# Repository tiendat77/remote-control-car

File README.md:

# Remote Control Car Project
> Remote control car with android and esp32

This project aims to build a Remote Control Car (RC Car) with Espressif ESP32 and Android Remote Control Application.

## Requirements :alien:
1. RC Car. Check out [building instructions](https://github.com/tiendat77/remote-control-car/tree/master/rc-car)
2. Android phone running 5.0 (Lollipop) or higher
3. WiFi network

## Usage :book:
1. Upload [the sketch](https://github.com/tiendat77/remote-control-car/blob/master/rc-car/rc-car.ino) to the RC Car via [Arduino IDE](https://www.arduino.cc/en/software)
2. Install [Car Controller](https://github.com/tiendat77/remote-control-car/blob/master/CarController.apk) application to your smartphone
3. Connect RC Car and your smartphone to the same WiFi network
4. Open Car Controller application, then open *App Settings* and make sure *RC Car IP Address* is correct.
5. Click `Connect Button` on the top left corner of the screen. *Light bulb on is connected*.
6. Enjoy!

## Features :muscle:
- Stable connection.
- Obstacles detection.
- Changeable themes.
- Supports 3 type of control: buttons, joystick, motion sensor (tilt to turn).

## Demos :boom:

## Future plans :eyes:

  - [ ] Install camera
  - [ ] Build wireless handle remote controller

## Contributing :sparkles:

If you have any problem from installation, please [open an issue](https://github.com/tiendat77/remote-control-car/issues/new).

Contributions of any kind are definitely welcome!

## Open source libraries
- [virtual-joystick-android](https://github.com/controlwear/virtual-joystick-android)

## License

MIT © 2020 [TienDat](mailto:huynhztienzdat@gmail.com), see [the license](https://github.com/tiendat77/remote-control-car/blob/master/LICENSE).

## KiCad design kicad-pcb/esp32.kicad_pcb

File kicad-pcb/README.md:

# KiCad
> KiCad is a free software suite for electronic design automation. It facilitates the design of schematics for electronic circuits and their conversion to PCB designs.

## Installation

[Download instructions](https://kicad.org/download/)

Install KiCad on Ubuntu, enter these commands into terminal:

```
sudo add-apt-repository --yes ppa:kicad/kicad-5.1-releases
sudo apt update
sudo apt install --install-recommends kicad

# If you want demo projects
sudo apt install kicad-demos
```

## RC Car Schematic
| PIN         | FUNCTION    | Description        |
| ----------- | ----------- | ------------------ |
| GPIO4       | L298N IN1   | L298N INPUT 1 (A1) |
| GPIO0       | L298N IN2   | L298N INPUT 2 (A2) |
| GPIO2       | L298N IN3   | L298N INPUT 3 (B1) |
| GPIO15      | L298N IN4   | L298N INPUT 4 (B2) |
| GPIO12      | SRF05 TRIG  | SRF05 TRIG (INPUT) |
| GPIO14      | SRF05 ECHO  | SRF05 ECHO (OUTPUT)|
| GPIO25      | SIGNAL      | WiFi connection status |
| GPIO33      | FUNCTION 1  | Headlight |
| GPIO32      | FUNCTION 2  | Left turn signal lights |
| GPIO35      | FUNCTION 3  | Right turn signal lights |
| GPIO34      | FUNCTION 4  | Horn |

## RC Car PCB
<table>
  <tr>
    <td></td>
    <td></td>
  </tr>
</table>

[PDF](https://github.com/tiendat77/remote-control-car/blob/master/assets/rc_car_pcb.pdf)

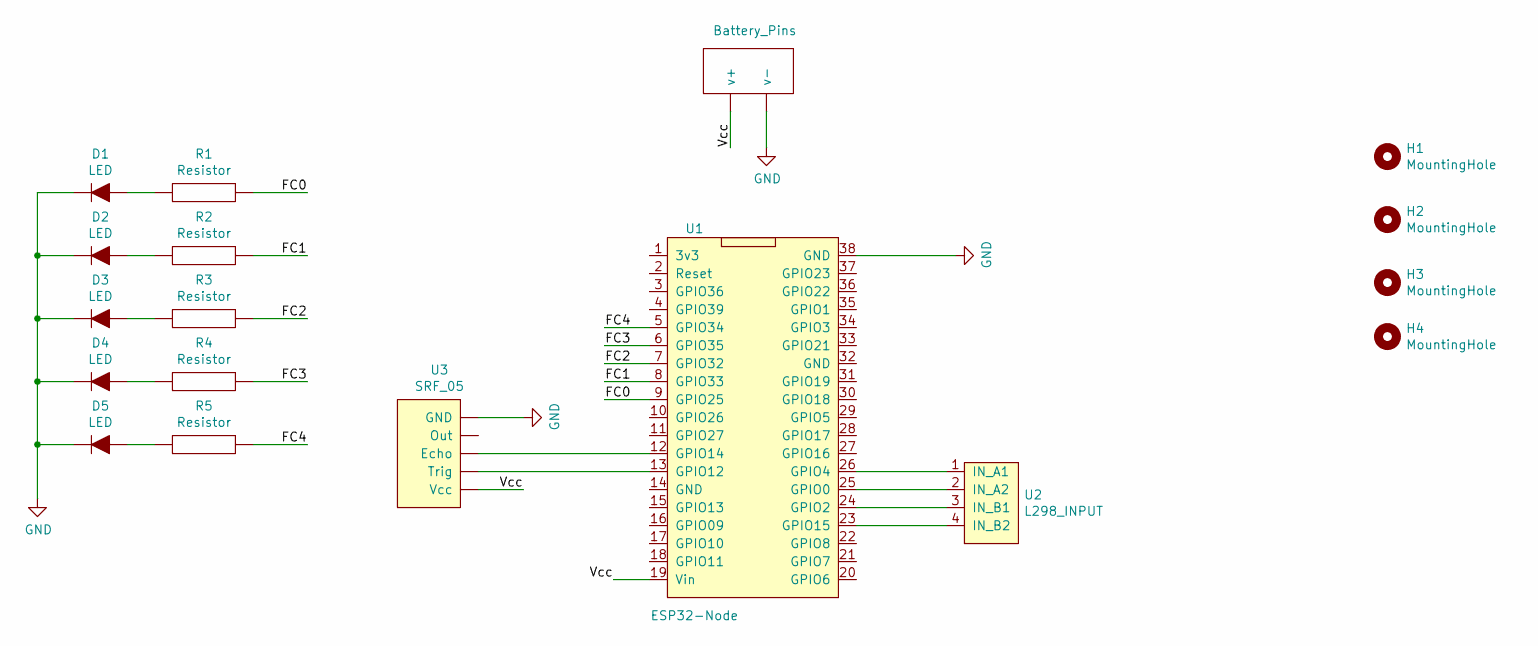
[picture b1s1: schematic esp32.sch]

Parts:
BT1: Battery_Pins; Domino_2_5.05mm
D1, D2, D3, D4, D5: LED; Led
H1, H2, H3, H4: MountingHole
R1, R2, R3, R4, R5: Resistor
U1: ESP32-Node; ESP32_Node
U2: L298_INPUT; L298_Input
U3: SRF_05; SRF05

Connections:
/FC0: R1.2, U1.9 (GPIO25)
/FC1: R2.2, U1.8 (GPIO33)
/FC2: R3.2, U1.7 (GPIO32)
/FC3: R4.2, U1.6 (GPIO35)
/FC4: R5.2, U1.5 (GPIO34)
/Vcc: BT1.1 (v+), U1.19 (Vin), U3.1 (Vcc)
GND: BT1.2 (v-), D1.2, D2.2, D3.2, D4.2, D5.2, U1.38 (GND), U3.5 (GND)
unnamed: D1.1, R1.1
unnamed: D2.1, R2.1
unnamed: D3.1, R3.1
unnamed: D4.1, R4.1
unnamed: D5.1, R5.1
unnamed: U1.12 (GPIO14), U3.3 (Echo)
unnamed: U1.13 (GPIO12), U3.2 (Trig)
unnamed: U1.23 (GPIO15), U2.4 (IN_B2)
unnamed: U1.24 (GPIO2), U2.3 (IN_B1)
unnamed: U1.25 (GPIO0), U2.2 (IN_A2)
unnamed: U1.26 (GPIO4), U2.1 (IN_A1)

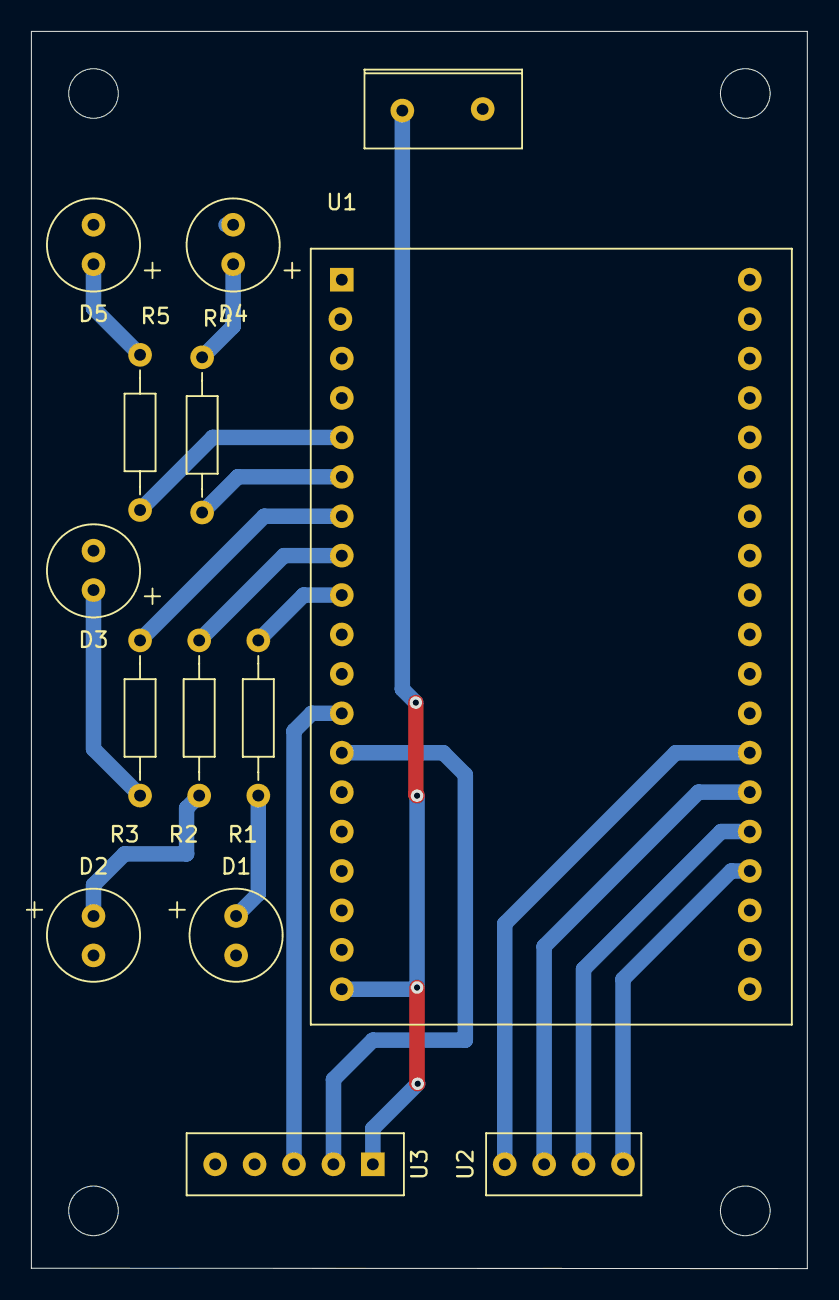
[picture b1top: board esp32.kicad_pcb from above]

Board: 2 copper layers, 50.0 x 79.7 mm, 18 parts (0 on the bottom side), 18 nets.

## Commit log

2020-11-10 Initial commit :sunrise:
2020-11-17 clean project
2020-11-19 feat(esp32): wifi server
2020-11-22 update esp
2020-11-22 esp with FreeRTOS
2020-11-23 init android project
2020-11-24 android template
2020-11-25 update android template
2020-11-26 android layout
2020-11-26 update test project
2020-11-26 update test proj
2020-11-26 update app layout
2020-11-27 server test
2020-11-27 feat: control view, tcp server test (#1)
    * esp wifi server with FreeRTOS
    * android control view
    * server test
2020-11-27 move virtual joystick library to local
2020-11-27 create controller package
2020-11-27 fix Setting Activity hidden UI navigation bar
2020-11-27 init README
2020-11-28 Create custom views, Rebase project
2020-11-28 app icon, splash screen
2020-11-28 feat: controller, app icon, splash screen (#2)
2020-11-29 update: server test
2020-11-29 update app icon
2020-11-29 feat accelerometer control
2020-11-29 clean assets
2020-11-29 feat: controlling by motion sensor (#3)
2020-11-30 update README and assets
2020-11-30 Update README (#4)
2020-11-30 feat: srf05
2020-12-01 udpate connection status
2020-12-04 update schematic
2020-12-06 feat: schematic and pcb
2020-12-06 feat: schematic and pcb (#5)
2020-12-06 update asset
2020-12-06 update doc
2020-12-06 update README (#6)
2020-12-07 feat: accelerometer animation
2020-12-08 fix: accelerometer animation
2020-12-08 customize virtual joystick library
2020-12-08 chore virtual joystick view
2020-12-09 update virtual joystick
2020-12-13 update app icons
2020-12-13 feat: accelerometer animation (#7)
    - change function icon
    - create JoystickView
    - create motion animation
